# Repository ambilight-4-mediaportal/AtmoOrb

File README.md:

# AtmoOrb

Projects / showcases using AtmoOrb:

### ESP8266
http://forum.team-mediaportal.com/threads/diy-atmoorb-a-hue-like-mood-lamp-based-on-arduino-esp8266-wifi-module-and-ws2812b-rgb-leds.129229/

### Spark / Particle (Core / Photon)
http://forum.team-mediaportal.com/threads/diy-atmoorb-a-hue-like-mood-lamp-based-on-particle-photon-with-neopixel-tutorial-added.131901/

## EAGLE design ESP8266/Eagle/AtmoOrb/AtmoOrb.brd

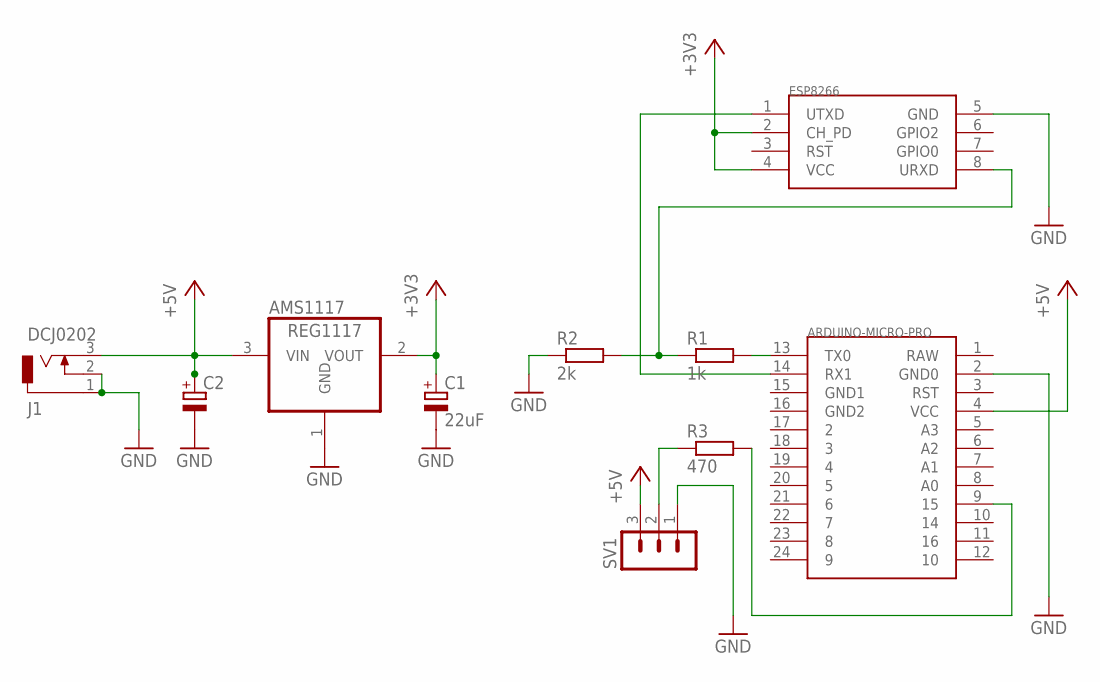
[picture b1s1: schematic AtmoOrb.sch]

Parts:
AMS1117: REG1117; SOT223
ARDUINO-MICRO-PRO: ARDUINO_MICRO_PRO
C1: 22uF; TAP5-60
C2: CPOL-EUTAP5-60; TAP5-60
ESP8266: ESP8266
J1: DCJ0202
R1: 1k; 0207/10
R2: 2k; 0207/10
R3: 470; 0207/10
SV1: MA03-1

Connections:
+3V3: AMS1117.2 (VOUT), C1.+, ESP8266.2 (CH_PD), ESP8266.4 (VCC)
+5V: AMS1117.3 (VIN), ARDUINO-MICRO-PRO.4 (VCC), C2.+, J1.3, SV1.3
GND: AMS1117.1 (GND), ARDUINO-MICRO-PRO.2 (GND0), C1.-, C2.-, ESP8266.5 (GND), J1.1, J1.2, R2.1, SV1.1
unnamed: ARDUINO-MICRO-PRO.13 (TX0), R1.2
unnamed: ESP8266.8 (URXD), R1.1, R2.2
unnamed: ARDUINO-MICRO-PRO.14 (RX1), ESP8266.1 (UTXD)
unnamed: ARDUINO-MICRO-PRO.9 (15), R3.2
unnamed: R3.1, SV1.2

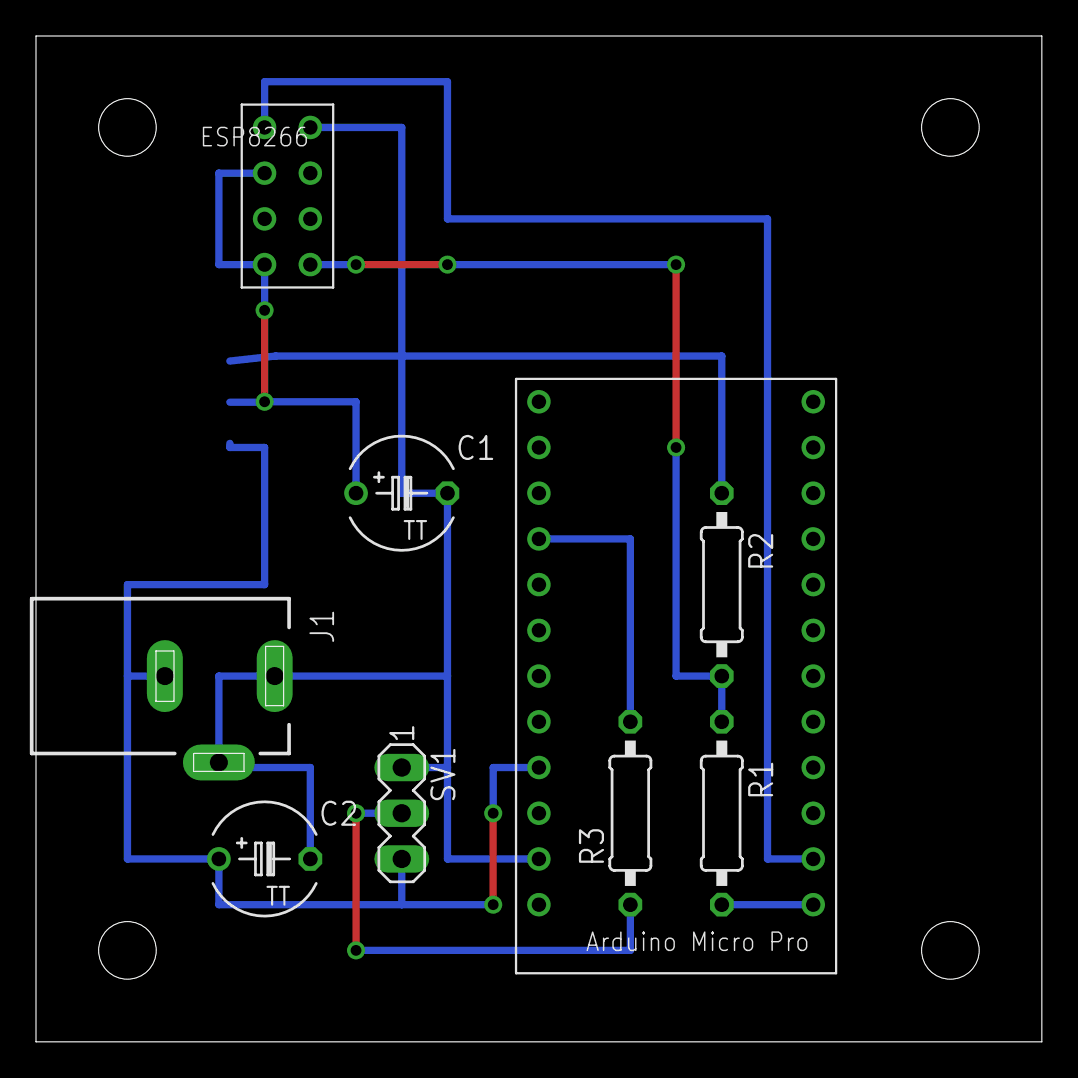
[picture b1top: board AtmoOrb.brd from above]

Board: 2 copper layers, 55.9 x 55.9 mm, 10 parts (1 on the bottom side), 8 nets.

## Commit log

2014-11-29 Arduino sketch and hardware schematics
2014-11-30 Added ip retrieval for older ESP8266 firmware. Deleted test code. When commands come in bunched together, only the last one will be used now. Using a millis "timer" now for ip retrieval instead of de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
2014-11-30 Updated schematic and board layout
2014-12-02 Added folder for CC3000 wifi module and moved ESP8266 stuff into its own folder
2014-12-02 Now using hex values for communication
2014-12-02 Added in FastLED
2014-12-02 Added submodule FastLED
2014-12-02 Added setcolors and getledcount commands
2014-12-02 Added initial Adafruit CC3000 sketch and library references
2014-12-02 Fixed submodules
2014-12-03 Added a switch to bring ESP8266 into update mode to schematic and board layout
2014-12-03 Some cleanup, added in ip validation and changing color after first connect
2014-12-03 Code cleanup, added getledgeo command
2014-12-03 Added UART passthrough sketch to tools
2014-12-04 Updated CC3000 sketch, tested and working with firmware 1.28. If you have an Wi-Fi password longer than 32 characters use the included CC3000 library from this repository.
2014-12-04 Changed CC3000 library reference, now points to fork that allows > 32 character Wi-Fi passwords.
2014-12-07 Added smoothing and lowered memory requirements
2014-12-07 Added ID, changed from RGB to GRB and changed broadcast message format
2014-12-08 Improved memory requirements and improved smoothing calculations
2014-12-08 Fixed smoothing. Before it was using nextColor as prevColor when smoothing got interrupted. This would result in hectic and wrong changes.
2014-12-08 Further memory optimization
2014-12-08 Got rid of delay in code and general cleanup
2014-12-09 Disabled RX and TX leds. Changed smoothing to calculate step size beforehand instead of ad-hoc.
2014-12-09 Changed smoothing solution and removed setcolors
2014-12-10 Added possibility to toggle blocking receiving setcolor commands during smoothing. Deleted deprecated commands and some code cleanup.
2014-12-14 Added white adjustment. Fixed bug in setSmoothColor. Changed standard port. Code cleanup.
2015-01-12 First draft of AtmoOrb with Spark Core support, supports UDP broadcast / setcolor.
2015-01-13 Added sketch with 433MHz RF transmitter
2015-01-15 Added Spark Core TCP as UDP is unstable due to the CC3000 library (frequent crashes), it now support mDNS as well to still allow easy setup without the need for an static IP address.
2015-01-15 Spark Core - tidy up code
2015-01-16 Spark Core - disconnect from spark cloud during active TCP connection to increase performance and stability, various fixes to make connections more stable.
2015-01-16 Spark Core - check if cloud disconnected before trying to connect again, smooth color fixes.
2015-01-16 Spark Core - only spawn TCP client once and not in loop.
2015-08-28 Added Particle Photon TCP support.
2015-08-28 Added mDNS to Photon. Updated SparkCore to use the same code as Phton because it's backwards compatible. Code cleanup and improvements.
2015-09-02 Added Particle Photon UDP support.
2015-09-02 Improved Particle Photon TCP data reading, disabled mDNS for now as broadcast is not yet support in the Photon firmware but will be in the next release. Copied over changes to forceLedsOFF() from the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
2015-09-12 Added Multicast group support to Photon
2015-09-12 Update AtmoOrb_UDP.ino
    Updated forceleds off to commandOptions
    Removed hostname as its no longer used
    Command option 1 is now force leds off
2015-09-12 Photon TCP protocol update
2015-09-12 Changed default multicast address for Photon so that's outside of the reserved ranges.
2015-09-12 Photon multicast IP changed to global setting
2015-09-13 Photon TCP / UDP updated to include Orb ID validation Cleaned up Photon TCP sketch
2015-09-13 Photon - check Orb ID for lights off command as well
2015-09-13 Photon - code cleanup
2015-09-14 Photon TCP - format changes
2015-09-20 Increased buffer size
2015-09-23 Tidy up folders for Particle devices Added udp.setBuffer to Photon UDP sketches
2015-09-26 Particle - added basic discovery support
2015-11-24 Particle - disabled forceLedsOFF() as repeated memset requests could crash code in some cases
2015-12-09 Photon UDP - switched to FastLED library and added optional smoothing override
2015-12-10 Photon TCP - switched to FastLED library and added optional smoothing override
2015-12-10 Photon UDP - removed debug options
2016-01-01 Photon UDP - enabled Particle multi-threading
2016-01-01 Photon TCP - enabled Particle multi-threading
2016-01-05 Photon UDP - added client respawning on WiFi interrupts
2016-01-05 Photon TCP - added client respawning on WiFi interrupts
2016-01-05 Photon UDP - added connectLock to prevent multiple reconnects
2016-01-05 Photon TCP - added connectLock to prevent multiple reconnects
2016-01-08 Photon - added FastLED color corrections for NeoPixel led ring.
2016-01-08 Photon UDP - removed client.Flush() as it slowed down processing
2016-01-09 Photon - simplified WiFi check
2016-01-09 Fixed communication problem between Arduino and ESP8266. Changed the way color correction is calculated. Changed start up color to be shown instantly rather than after wifi connection.
2016-01-10 Photon - can now choose between custom or predefined color corrections
2016-01-14 Photon - disabled forceLedsOFF()
2016-01-17 Added project links
2016-02-05 WiFi check are now called every minute. Corrected code indenting and removed old code.
2016-02-05 Photon - code cleanup and corrections
2016-02-06 Photon - removed extra variable
2016-02-06 Photon - increased WiFi check times. Workaround for firmware issue as clients don't respawn during network interrupts and if WiFi reconnects fast enough the clients don't get recreated.
2016-02-06 Photon - black <-> color now always overrides smoothing
2016-03-24 Added ESP8266 Standalone support
2016-03-28 Added RC-Switch lib as Submodule
2016-03-28 Added ESP8266 Core library
2016-03-30 Updated AtmoOrb ESP8266 Standalone sketch
2016-03-31 Photon sketches now compatible with latest smoothing changes (AtmoLight / Hyperion).
2016-04-08 Added optional feature to dim the single built-in led in setup().
2016-04-09 ESP8266 fixes. Fixed led data transmission being interrupted. Tweaked smoothing default values. Fixed RCSwitch not working. Added WiFi connection lost debugging. Updated FastLED library.
2016-04-09 Rollback some Photon sketch changes.
2016-04-11 Photon sketches cleaned up and restored some previously removed code.
2016-04-11 Photon - enabled smoothing by default and added single led control to TCP as well
2016-04-11 Photon - removed obsolete smoothing check as that will be handled at the sender end soon.
2016-05-02 Store smooth color for non-smoothing command type as well. Dim internal Photon led by default.
2016-08-29 No need to include RCSwitch if it's disabled anyhow
2016-09-30 Corrected typo in Photon sketches
2016-12-31 Fixed bug in WiFi connection detection
2017-03-31 Added H801 (esp8266) code
2017-03-31 fixed rst formatting errors
2017-11-17 Update ESP8266_H801.ino
    I noticed that the ESP is still broadcasting its own "wifi network" by default. It shows up in my available wifi networks as ESP_xxxxxx where xxxxxx is the ID number of my ESP. Even if it is alreay c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
    I found the solution for the ESP broadcasting it's own network.
    Just symply add this line in the code for the H801:
    WiFi.mode(WIFI_STA);
    I placed this line just above the already existing line:
    WiFi.begin(ssid, password);
2019-12-30 Cleanup and new WiFi check
    Improved WiFi check with timeout (WaitFor method)
    Testing with latest Photon firmware (1.4.4)
2019-12-30 Better way of handling WiFi reconnects
    Added delays to reconnect to reliable (re)create UDP client
